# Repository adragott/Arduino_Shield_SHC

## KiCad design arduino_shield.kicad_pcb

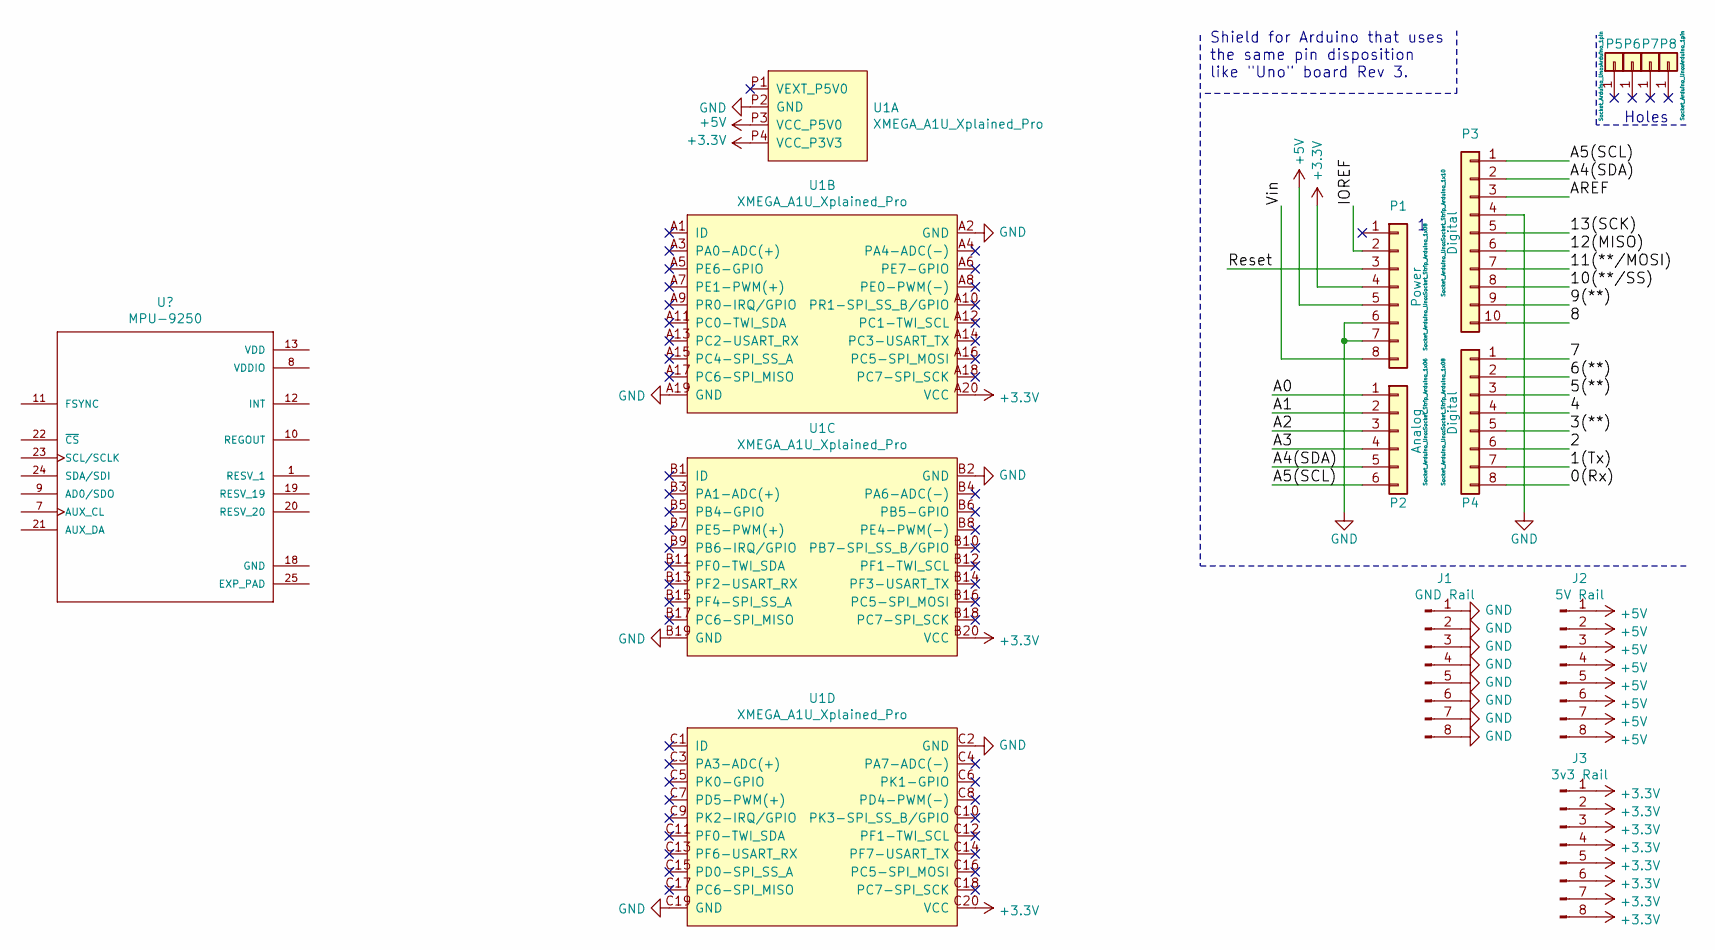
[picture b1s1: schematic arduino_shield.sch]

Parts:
J1: GND Rail; PinHeader_1x08_P2.54mm_Vertical
J2: 5V Rail; PinHeader_1x08_P2.54mm_Vertical
J3: 3v3 Rail; PinHeader_1x08_P2.54mm_Vertical
P1: Power; Socket_Strip_Arduino_1x08
P2: Analog; Socket_Strip_Arduino_1x06
P3: Digital; Socket_Strip_Arduino_1x10
P4: Digital; Socket_Strip_Arduino_1x08
P5, P6, P7, P8: CONN_01X01; Arduino_1pin
U1: XMEGA_A1U_Xplained_Pro; XMEGA_XPLAINED_AU

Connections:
+3V3: J3.1, J3.2, J3.3, J3.4, J3.5, J3.6, J3.7, J3.8, P1.4, U1.A20 (VCC), U1.B20 (VCC), U1.C20 (VCC), U1.P4 (VCC_P3V3)
+5V: J2.1, J2.2, J2.3, J2.4, J2.5, J2.6, J2.7, J2.8, P1.5, U1.P3 (VCC_P5V0)
/0(Rx): P4.8
/1(Tx): P4.7
/2: P4.6
/3(**): P4.5
/4: P4.4
/5(**): P4.3
/6(**): P4.2
/7: P4.1
/8: P3.10
/9(**): P3.9
/10(**/SS): P3.8
/11(**/MOSI): P3.7
/12(MISO): P3.6
/13(SCK): P3.5
/A0: P2.1
/A1: P2.2
/A2: P2.3
/A3: P2.4
/A4(SDA): P2.5, P3.2
/A5(SCL): P2.6, P3.1
/AREF: P3.3
/IOREF: P1.2
/Reset: P1.3
/Vin: P1.8
GND: J1.1, J1.2, J1.3, J1.4, J1.5, J1.6, J1.7, J1.8, P1.6, P1.7, P3.4, U1.A2 (GND), U1.A19 (GND), U1.B2 (GND), U1.B19 (GND), U1.C2 (GND), U1.C19 (GND), U1.P2 (GND)

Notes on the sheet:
Holes
Shield for Arduino that uses the same pin disposition like "Uno" board Rev 3.

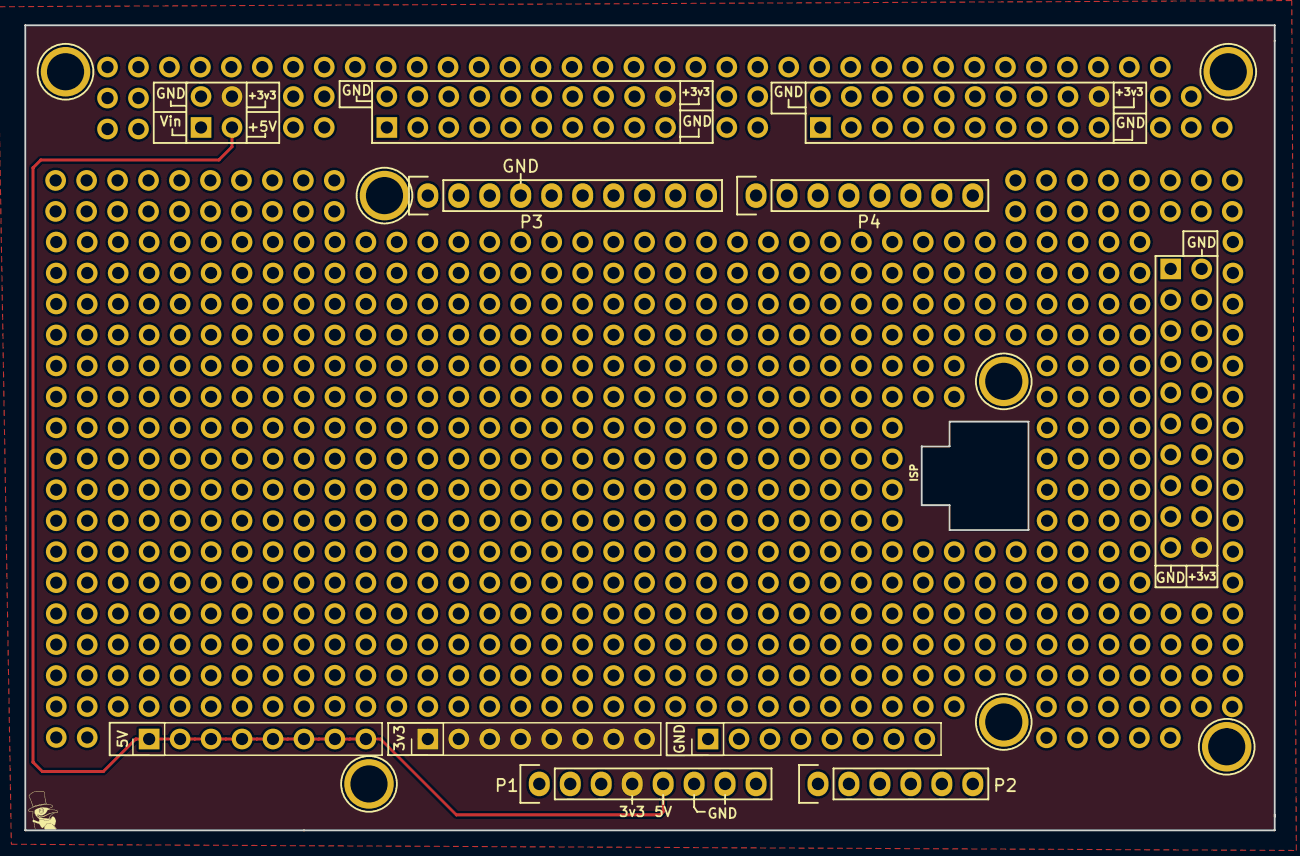
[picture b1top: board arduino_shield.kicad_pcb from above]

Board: 2 copper layers, 102.5 x 66.0 mm, 15 parts (0 on the bottom side), 5 nets.

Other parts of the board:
P7#2, P7#3, P7#4: CONN_01X01; Arduino_1pin

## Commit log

2019-06-19 init
2019-07-21 finished maybe?
2019-07-21 Fixed gerber issue
2019-07-21 Fixed even more!
2019-08-04 Added silkscreen and fixed the bow tie
2019-10-06 added pdf for schematic
2019-10-06 added 3d preview image
